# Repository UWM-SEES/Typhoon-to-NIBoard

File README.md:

# Typhoon to National Instruments Interface Board

## Overview
This interface board was designed to connect Typhoon HIL hardware to National Instruments PXIe-7862 FPGA cards. It provides a hardware interface between Typhoon HIL systems using DIN41612 3×32 connectors and the NI SHC68-68-RMIO cable used by the PXIe-7862.

The board uses the connector spacing from the Typhoon HIL Breakout Board R3.3, which is available from the Typhoon HIL website.

The interface allows signals from the Typhoon HIL system to be routed to one or two NI PXIe-7862 cards.

---

## Hardware Compatibility

### Typhoon HIL
Any Typhoon HIL system supporting:
- Two DIN41612 3×32 connectors

### National Instruments
- PXIe-7862 FPGA cards
- SHC68-68-RMIO cables

---

## Multi-Card Support

The PXIe-7862 connector has a limited number of analog output channels.

Because of this:

- The interface board can operate with **one PXIe-7862 card**
- It can also connect to **two PXIe-7862 cards**

When using two cards, additional analog outputs become available.

When using only one card, the analog outputs routed to the second connector will not be used.

---

## Analog Signal Behavior

Typhoon HIL outputs **single-ended analog signals**, not differential signals.

Therefore:

- The PXIe-7862 **analog input (+)** receives the signal.
- The **analog input (-)** is **not connected** on this interface board.

---

## Grounding

Typhoon HIL uses shared grounds rather than per-channel grounds.

### Analog
All analog channels share **one analog ground**

### Digital
All digital channels share **one digital ground**

### Important
Analog ground and digital ground are **separate from each other**.

---

## Digital I/O Configuration

Typhoon and NI handle digital signals differently.

### Typhoon
Digital inputs and outputs are on **separate pins**.

### PXIe-7862
Digital pins are **configurable as either input or output**.

---

## Direction Selection Switches

To support this difference, the interface board includes switches that select the signal direction.

Each digital channel can be configured for:

- **NI Input (Typhoon Output)**
- **NI Output (Typhoon Input)**

If you want:

- NI to read a signal → set the switch to **NI Input / Typhoon Output**
- NI to drive a signal → set the switch to **NI Output / Typhoon Input**

All switches are labeled directly on the PCB and referenced in the pinout diagram.

---

## Pinout Diagram

---

## Notes

- Analog inputs are single-ended.
- Analog negative pins on the NI side are unused.
- Digital signals require direction selection via switches.
- Two NI cards can be used to increase available analog outputs.

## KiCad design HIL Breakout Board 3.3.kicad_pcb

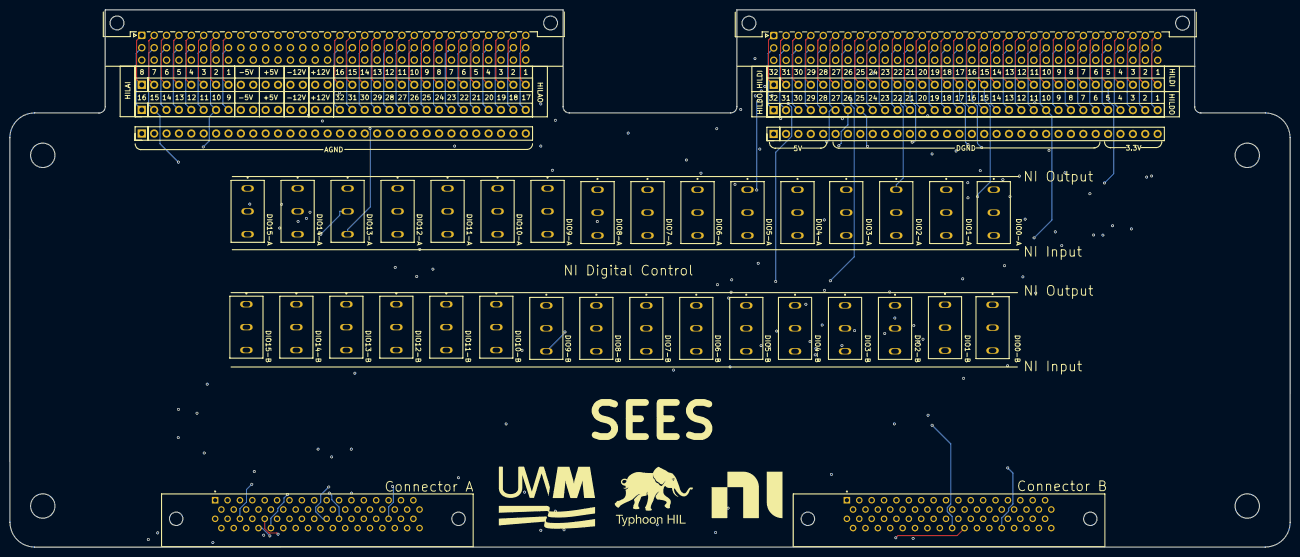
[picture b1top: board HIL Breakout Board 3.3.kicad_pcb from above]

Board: 6 copper layers, 262.5 x 110.2 mm, 42 parts (0 on the bottom side), 152 nets.

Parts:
J1, J2: DIN41612_03x32_C_Split; DIN41612_R_3x32_Female_Horizontal_THT
J3, J6, J7, J8, J9, J10: Conn_01x32_Pin; PinHeader_1x32_P2.54mm_Vertical
J4, J5: 2-5174225-5; TE_2-5174225-5
S1, S2, S3, S4, S5, S6, S7, S8, S9, S10, S11, S12, S13, S14, S15, S16, S17, S18, S19, S20, S21, S22, S23, S24, S25, S26, S27, S28, S29, S30, S31, S32: SLW-1276864-4A-D; SW_SLW-1276864-4A-D

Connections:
3.3VDout: J2.c28, J2.c29, J2.c30, J2.c31, J2.c32, J3.28, J3.29, J3.30, J3.31, J3.32
5VDout: J2.c1, J2.c2, J2.c3, J2.c4, J2.c5, J3.1, J3.2, J3.3, J3.4, J3.5
+5V: J1.a11, J1.a12, J1.b11, J1.b12, J9.11, J9.12, J10.11, J10.12
+12V: J1.a15, J1.a16, J1.b15, J1.b16, J9.15, J9.16, J10.15, J10.16
-5V: J1.a9, J1.a10, J1.b9, J1.b10, J9.9, J9.10, J10.9, J10.10
-12V: J1.a13, J1.a14, J1.b13, J1.b14, J9.13, J9.14, J10.13, J10.14
AGND: J1.c1, J1.c2, J1.c3, J1.c4, J1.c5, J1.c6, J1.c7, J1.c8, J1.c9, J1.c10, J1.c11, J1.c12, J1.c13, J1.c14, J1.c15, J1.c16, J1.c17, J1.c18, J1.c19, J1.c20, J1.c21, J1.c22, J1.c23, J1.c24, J1.c25, J1.c26, J1.c27, J1.c28, J1.c29, J1.c30, J1.c31, J1.c32, J4.A14, J4.A15, J4.A16, J4.A17, J4.A18, J4.A19, J4.A20, J4.A21, J4.A24, J4.A27, J4.A30, J4.A33, J4.B24, J4.B27, J4.B30, J4.B33, J5.A14, J5.A15, J5.A16, J5.A17, J5.A18, J5.A19, J5.A20, J5.A21, J5.A24, J5.A27, J5.A30, J5.A33, J5.B24, J5.B27, J5.B30, J5.B33, J8.1, J8.2, J8.3, J8.4, J8.5, J8.6, J8.7, J8.8, J8.9, J8.10, J8.11, J8.12, J8.13, J8.14, J8.15, J8.16, J8.17, J8.18, J8.19, J8.20, J8.21, J8.22, J8.23, J8.24, J8.25, J8.26, J8.27, J8.28, J8.29, J8.30, J8.31, J8.32
AI1: J1.a8, J4.B21, J10.8
AI2: J1.a7, J4.B20, J10.7
AI3: J1.a6, J4.B19, J10.6
AI4: J1.a5, J4.B18, J10.5
AI5: J1.a4, J4.B17, J10.4
AI6: J1.a3, J4.B16, J10.3
AI7: J1.a2, J4.B15, J10.2
AI8: J1.a1, J4.B14, J10.1
AI9: J1.b8, J5.B21, J9.8
AI10: J1.b7, J5.B20, J9.7
AI11: J1.b6, J5.B19, J9.6
AI12: J1.b5, J5.B18, J9.5
AI13: J1.b4, J5.B17, J9.4
AI14: J1.b3, J5.B16, J9.3
AI15: J1.b2, J5.B15, J9.2
AI16: J1.b1, J5.B14, J9.1
AO1: J1.a32, J4.B34, J10.32
AO2: J1.a31, J4.B32, J10.31
AO3: J1.a30, J4.B31, J10.30
AO4: J1.a29, J4.B29, J10.29
AO5: J1.a28, J4.B28, J10.28
AO6: J1.a27, J4.B26, J10.27
AO7: J1.a26, J4.B25, J10.26
AO8: J1.a25, J4.B23, J10.25
AO9: J1.a24, J5.B34, J10.24
AO10: J1.a23, J5.B32, J10.23
AO11: J1.a22, J5.B31, J10.22
AO12: J1.a21, J5.B29, J10.21
AO13: J1.a20, J5.B28, J10.20
AO14: J1.a19, J5.B26, J10.19
AO15: J1.a18, J5.B25, J10.18
AO16: J1.a17, J5.B23, J10.17
AO17: J1.b32, J9.32
AO18: J1.b31, J9.31
AO19: J1.b30, J9.30
AO20: J1.b29, J9.29
AO21: J1.b28, J9.28
AO22: J1.b27, J9.27
AO23: J1.b26, J9.26
AO24: J1.b25, J9.25
AO25: J1.b24, J9.24
AO26: J1.b23, J9.23
AO27: J1.b22, J9.22
AO28: J1.b21, J9.21
AO29: J1.b20, J9.20
AO30: J1.b19, J9.19
AO31: J1.b18, J9.18
AO32: J1.b17, J9.17
DGND: J2.c6, J2.c7, J2.c8, J2.c9, J2.c10, J2.c11, J2.c12, J2.c13, J2.c14, J2.c15, J2.c16, J2.c17, J2.c18, J2.c19, J2.c20, J2.c21, J2.c22, J2.c23, J2.c24, J2.c25, J2.c26, J2.c27, J3.6, J3.7, J3.8, J3.9, J3.10, J3.11, J3.12, J3.13, J3.14, J3.15, J3.16, J3.17, J3.18, J3.19, J3.20, J3.21, J3.22, J3.23, J3.24, J3.25, J3.26, J3.27, J4.A2, J4.A3, J4.A4, J4.A5, J4.A6, J4.A7, J4.A8, J4.A9, J5.A2, J5.A3, J5.A4, J5.A5, J5.A6, J5.A7, J5.A8, J5.A9
DI1: J2.a32, J7.32, S1.1
DI2: J2.a31, J7.31, S2.1
DI3: J2.a30, J7.30, S3.1
DI4: J2.a29, J7.29, S4.1
DI5: J2.a28, J7.28, S5.1
DI6: J2.a27, J7.27, S6.1
DI7: J2.a26, J7.26, S7.1
DI8: J2.a25, J7.25, S8.1
DI9: J2.a24, J7.24, S9.1
DI10: J2.a23, J7.23, S10.1
DI11: J2.a22, J7.22, S11.1
DI12: J2.a21, J7.21, S12.1
DI13: J2.a20, J7.20, S13.1
DI14: J2.a19, J7.19, S14.1
DI15: J2.a18, J7.18, S15.1
DI16: J2.a17, J7.17, S16.1
DI17: J2.a16, J7.16, S17.1
DI18: J2.a15, J7.15, S18.1
DI19: J2.a14, J7.14, S19.1
DI20: J2.a13, J7.13, S20.1
DI21: J2.a12, J7.12, S21.1
DI22: J2.a11, J7.11, S22.1
DI23: J2.a10, J7.10, S23.1
DI24: J2.a9, J7.9, S24.1
DI25: J2.a8, J7.8, S25.1
DI26: J2.a7, J7.7, S26.1
DI27: J2.a6, J7.6, S27.1
DI28: J2.a5, J7.5, S28.1
DI29: J2.a4, J7.4, S29.1
DI30: J2.a3, J7.3, S30.1
DI31: J2.a2, J7.2, S31.1
DI32: J2.a1, J7.1, S32.1
DO1: J2.b32, J6.32, S1.3
DO2: J2.b31, J6.31, S2.3
DO3: J2.b30, J6.30, S3.3
DO4: J2.b29, J6.29, S4.3
DO5: J2.b28, J6.28, S5.3
DO6: J2.b27, J6.27, S6.3
DO7: J2.b26, J6.26, S7.3
DO8: J2.b25, J6.25, S8.3
DO9: J2.b24, J6.24, S9.3
DO10: J2.b23, J6.23, S10.3
DO11: J2.b22, J6.22, S11.3
DO12: J2.b21, J6.21, S12.3
DO13: J2.b20, J6.20, S13.3
DO14: J2.b19, J6.19, S14.3
DO15: J2.b18, J6.18, S15.3
DO16: J2.b17, J6.17, S16.3
DO17: J2.b16, J6.16, S17.3
DO18: J2.b15, J6.15, S18.3
DO19: J2.b14, J6.14, S19.3
DO20: J2.b13, J6.13, S20.3
DO21: J2.b12, J6.12, S21.3
DO22: J2.b11, J6.11, S22.3
DO23: J2.b10, J6.10, S23.3
DO24: J2.b9, J6.9, S24.3
DO25: J2.b8, J6.8, S25.3
DO26: J2.b7, J6.7, S26.3
DO27: J2.b6, J6.6, S27.3
DO28: J2.b5, J6.5, S28.3
DO29: J2.b4, J6.4, S29.3
DO30: J2.b3, J6.3, S30.3
DO31: J2.b2, J6.2, S31.3
DO32: J2.b1, J6.1, S32.3
unnamed: J4.A10, S9.2
unnamed: J4.A11, S11.2
unnamed: J4.A12, S13.2
unnamed: J4.A13, S15.2
unnamed: J4.B2, S1.2
unnamed: J4.B3, S2.2
unnamed: J4.B4, S3.2
unnamed: J4.B5, S4.2
unnamed: J4.B6, S5.2
unnamed: J4.B7, S6.2
unnamed: J4.B8, S7.2
unnamed: J4.B9, S8.2
unnamed: J4.B10, S10.2
unnamed: J4.B11, S12.2
unnamed: J4.B12, S14.2
unnamed: J4.B13, S16.2
unnamed: J5.A10, S25.2
unnamed: J5.A11, S27.2
unnamed: J5.A12, S29.2
unnamed: J5.A13, S31.2
unnamed: J5.B2, S17.2
unnamed: J5.B3, S18.2
unnamed: J5.B4, S19.2
unnamed: J5.B5, S20.2
unnamed: J5.B6, S21.2
unnamed: J5.B7, S22.2
unnamed: J5.B8, S23.2
unnamed: J5.B9, S24.2
unnamed: J5.B10, S26.2
unnamed: J5.B11, S28.2
unnamed: J5.B12, S30.2
unnamed: J5.B13, S32.2

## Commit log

2025-11-13 Added switches for A side
2025-11-14 Added all DC inputs and outputs for B side of connector
2025-11-14 Added Digital and Analog Grounds Added AN Outputs into A and B
2025-11-14 Added all analog inputs and outputs to schematic Schematic still missing +5 V on pin 1 and 35 and AISENSE1 on pin 56 for A and B side Updated PCB Design
2025-11-17 Fixed the issue with naming of net labels so that all digital pins were not tied together
2025-11-17 Got rid of all names of wires because it was causing issues with global variables Started PCB tracks
2025-11-19 Added all analog traces Changed NI connection to two separate ports Added footprint folders for switch and NI connector
2025-11-19 Added traces from all switches to NI connector
2025-11-19 Added all NI input signals to switches
2025-11-20 Finished all traces on pcb Added labels for all digital switches with connector A and B
2025-11-20 Rounded edges of board
2025-11-20 Added mounting holes
2025-11-21 Refined traces for analog outputs
2025-11-21 Refined Analog Input Traces
2025-11-21 Spaced out traces between switches so they don't overlap at all
2025-11-24 Refined all traces so there is no overlap on adjacent layers and now sharp corners through a via
2026-03-11 Create README.md
    Created a readme file for how to use the interface board
2026-03-11 Added pinout image
2026-03-19 Flipped pins
    Filled the pinouts of the Typhoon Connectors and added pins for easier trace testing. Will be making many more changes
2026-04-10 Fixed the board and added logos
2026-04-10 Kevin
    Hi Kevin
2026-04-10 Fixed the logo placement and added SEES
2026-04-13 Minor changes to board
